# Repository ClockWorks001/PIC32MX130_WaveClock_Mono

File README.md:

# PIC32MX130F Speaking Clock Project.
---
This is a wave player  project with PIC32MX130 micro controller.
It can speak a "time" by using wave files which are stored in a SD card. 
And it also can play music wave files.

## Description

References.
  <http://microchip.wikidot.com/>

## Prerequisites

I created this project using the free versions of the following tools:
 * [Microchip MPLAB X][2] (v3.35)
 * [Microchip XC32 Compiler][3] (v1.3)
 * [EAGLE][6] (v4.0.1)

You will need to download and install these tools appropriately before you
can open this project and build it.
I use the [Microchip MPLAB PICkit3 In-Circuit Debugger][5] to program the chip and debug it.  

Also, I use the [EAGLE][6] to draw the electric circuit schematic.

## Licence

[MIT](https://github.com/tcnksm/tool/blob/master/LICENCE)

## Author

Hiroshi Murakami  
<https://github.com/ClockWorks001>  

[1]: http://ww1.microchip.com/downloads/en/DeviceDoc/60001168F.pdf "PIC32MXxxx"
[2]: http://www.microchip.com/pagehandler/en-us/family/mplabx/ "MPLAB X"
[3]: http://www.microchip.com/pagehandler/en_us/devtools/mplabxc/ "MPLAB XC Compilers"
[4]: http://www.microchip.com/harmony "MPLAB Harmony Configurator"
[5]: http://www.microchip.com/Developmenttools/ProductDetails.aspx?PartNO=PG164130 "MPLAB PICkit3 In-Circuit Debugger"
[6]: https://cadsoft.io/ "EAGLE"

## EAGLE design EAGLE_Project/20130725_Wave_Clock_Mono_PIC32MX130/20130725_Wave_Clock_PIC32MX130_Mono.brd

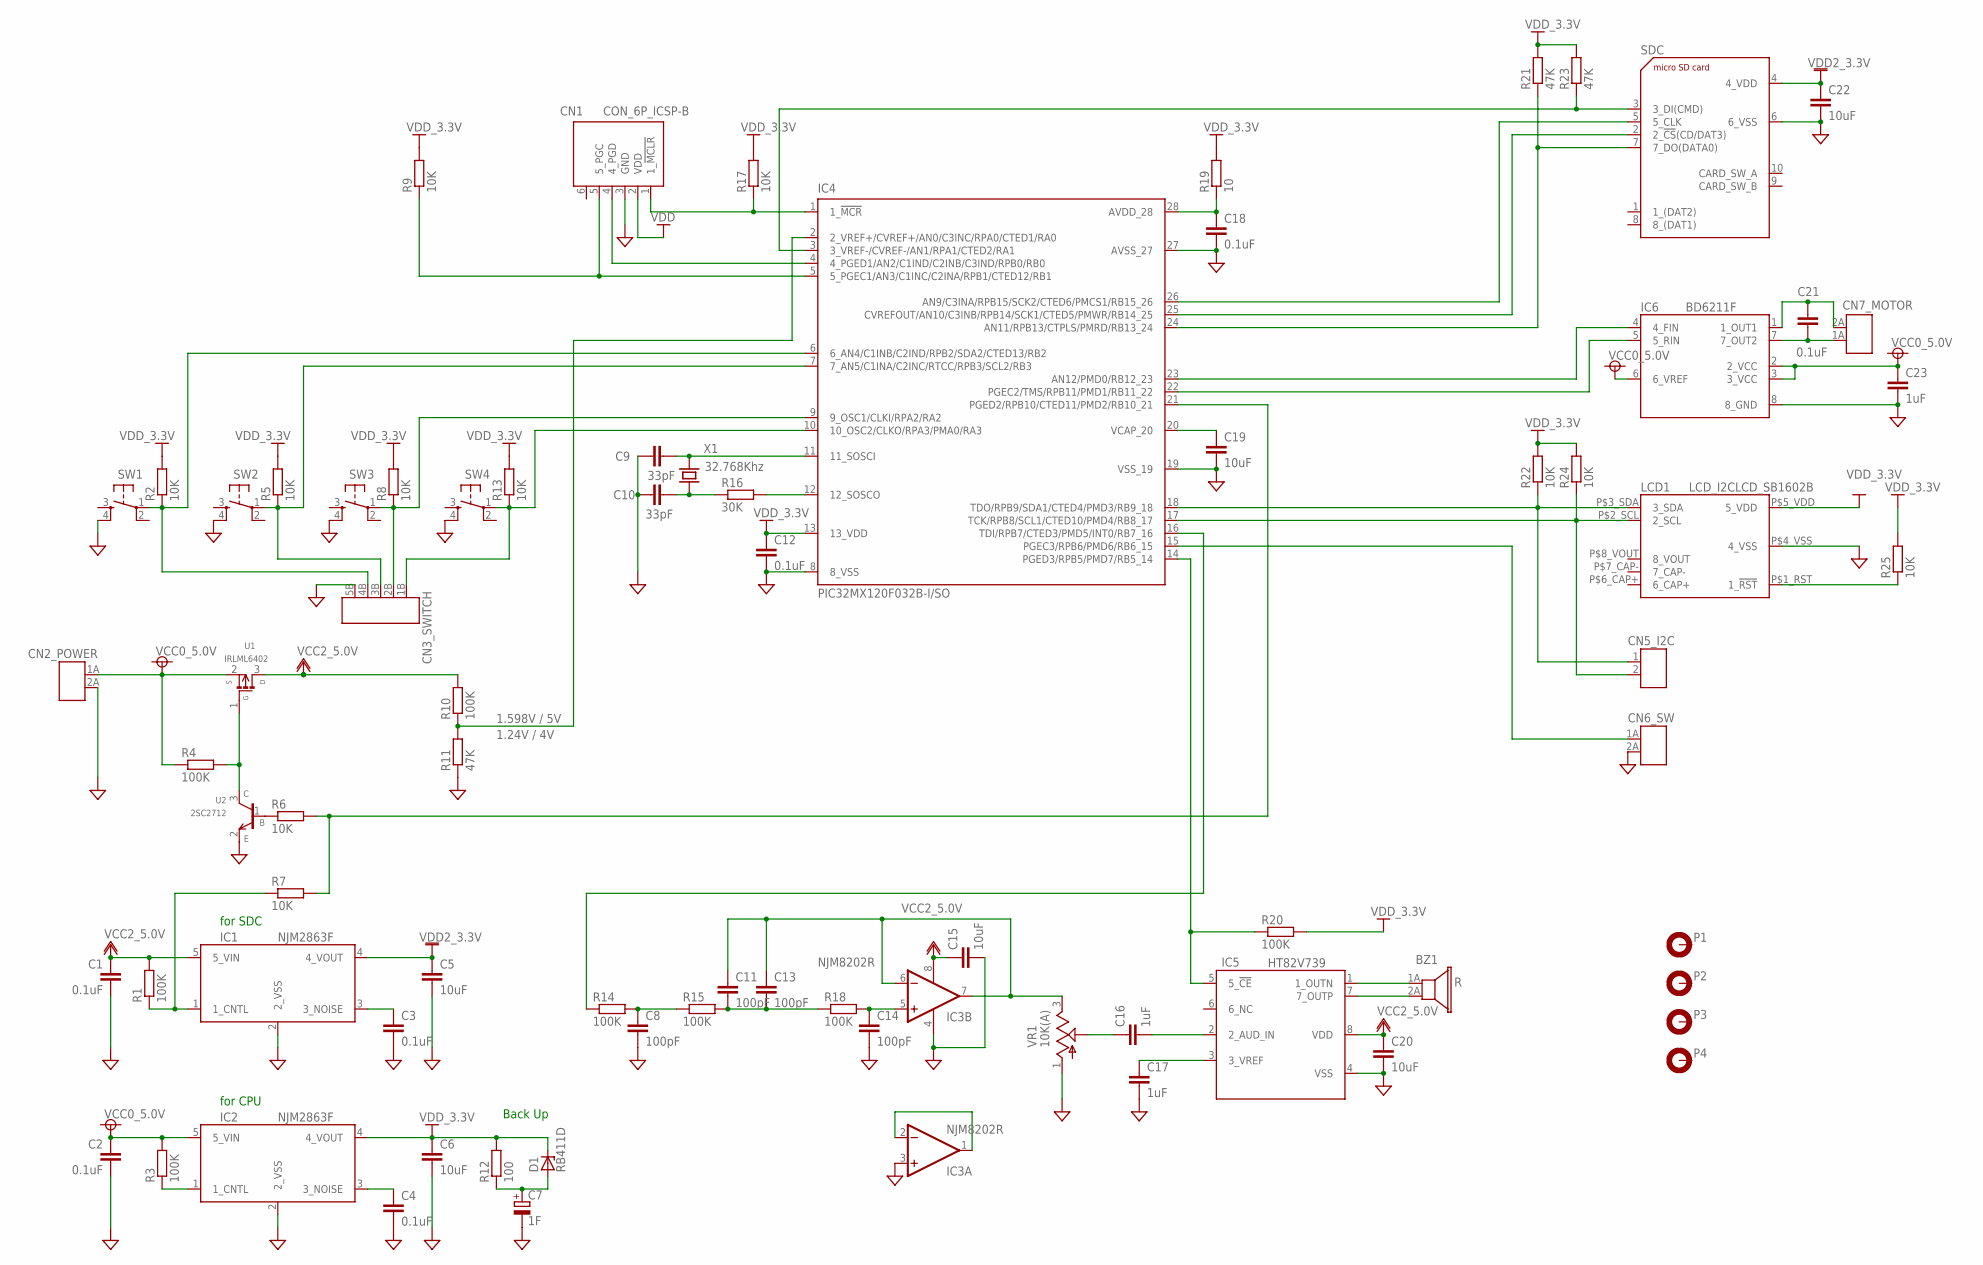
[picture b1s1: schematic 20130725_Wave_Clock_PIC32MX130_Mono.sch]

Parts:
BZ1: R; TERMINAL_AH-2P
C1, C2, C3, C4, C12, C18, C21: 0.1uF; 1608
C5, C6, C15, C19, C20, C22: 10uF; 3216
C7: 1F; E5-19V-B
C8, C11, C13, C14: 100pF; 1608
C9, C10: 33pF; 1608
C16, C17, C23: 1uF; 1608
CN1: CON_6P_ICSP-B; CON_DIP_6-B
CN2_POWER, CN6_SW, CN7_MOTOR: CON_2P-B; TERMINAL_AH-2P
CN3_SWITCH: CON_5PVR; TERMINAL_AV-5P
CN5_I2C: CON_2P-B; CON_DIP_2-B
D1: RB411D; SOT-23-3-2915-B
IC1, IC2: NJM2863F; SOT-23-5-2916-B
IC3: NJM8202R; MSOP08
IC4: PIC32MX120F032B-I/SO; SO28W
IC5: HT82V739; DIP08-B
IC6: BD6211F; SOP8
LCD1: LCD_I2CLCD_SB1602B; LCD_SB1602B
P1, P2, P3, P4: MOUNT-PAD3.3; PAD-3.3-B
R1, R3, R4, R10, R14, R15, R18, R20: 100K; 1608
R2, R5, R6, R7, R8, R9, R13, R17, R22, R24, R25: 10K; 1608
R11, R21, R23: 47K; 1608
R12: 100; 1608
R16: 30K; 1608
R19: 10; 1608
SDC: DM3AT-SF-PEJＤ; DM3AT-SF-DIP
SW1, SW2, SW3, SW4: SW_TACT1; SW_TACT-B
U1: IRLML6402; SC-59-2915
U2: 2SC2712; SOT-23-3-2915-B
VR1: 10K(A); VOL_MIDDLE
X1: 32.768Khz; VT-200

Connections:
GND: C1.2, C2.2, C3.2, C4.2, C5.2, C6.2, C7.-, C8.2, C9.2, C10.2, C12.2, C14.2, C15.2, C17.2, C18.2, C19.2, C20.2, C22.2, C23.2, CN1.3 (GND), CN2_POWER.2A (2), CN3_SWITCH.5B (5), CN6_SW.2A (2), IC1.2 (2_VSS), IC2.2 (2_VSS), IC3.3 (+IN), IC3.4 (V-), IC4.8 (8_VSS), IC4.19 (VSS_19), IC4.27 (AVSS_27), IC5.4 (VSS), IC6.8 (8_GND), LCD1.P$4_VSS (4_VSS), R11.1, SDC.6 (6_VSS), SW1.4 (S1), SW2.4 (S1), SW3.4 (S1), SW4.4 (S1), U2.2 (E), VR1.1 (A)
unnamed: CN1.1 (1_!MCLR), IC4.1 (1_!MCR), R17.1
unnamed: CN1.5 (5_PGC), IC4.5 (5_PGEC1/AN3/C1INC/C2INA/RPB1/CTED12/RB1), R9.1
unnamed: C18.1, IC4.28 (AVDD_28), R19.1
unnamed: C19.1, IC4.20 (VCAP_20)
unnamed: IC4.12 (12_SOSCO), R16.2
unnamed: C9.1, IC4.11 (11_SOSCI), X1.P$2 (2)
unnamed: CN1.4 (4_PGD), IC4.4 (4_PGED1/AN2/C1IND/C2INB/C3IND/RPB0/RB0)
unnamed: CN5_I2C.2, IC4.17 (TCK/RPB8/SCL1/CTED10/PMD4/RB8_17), LCD1.P$2_SCL (2_SCL), R24.1
unnamed: CN5_I2C.1, IC4.18 (TDO/RPB9/SDA1/CTED4/PMD3/RB9_18), LCD1.P$3_SDA (3_SDA), R22.1
unnamed: LCD1.P$1_RST (1_!RST), R25.1
unnamed: IC4.26 (AN9/C3INA/RPB15/SCK2/CTED6/PMCS1/RB15_26), SDC.5 (5_CLK)
unnamed: IC4.24 (AN11/RPB13/CTPLS/PMRD/RB13_24), R21.1, SDC.7 (7_DO(DATA0))
unnamed: IC4.25 (CVREFOUT/AN10/C3INB/RPB14/SCK1/CTED5/PM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), SDC.2 (2_!CS!(CD/DAT3))
unnamed: IC4.3 (3_VREF-/CVREF-/AN1/RPA1/CTED2/RA1), R23.1, SDC.3 (3_DI(CMD))
unnamed: CN3_SWITCH.2B (2), IC4.9 (9_OSC1/CLKI/RPA2/RA2), R8.1, SW3.1
unnamed: IC4.16 (TDI/RPB7/CTED3/PMD5/INT0/RB7_16), R14.1
unnamed: C14.1, IC3.5 (+IN), R18.2
unnamed: C8.1, R14.2, R15.1
unnamed: C11.2, C13.2, R15.2, R18.1
unnamed: IC3.1 (OUT), IC3.2 (-IN)
unnamed: CN6_SW.1A (1), IC4.15 (PGEC3/RPB6/PMD6/RB6_15)
unnamed: C17.1, IC5.3 (3_VREF)
unnamed: C16.2, IC5.2 (2_AUD_IN)
unnamed: BZ1.1A, IC5.1 (1_OUTN)
unnamed: BZ1.2A, IC5.7 (7_OUTP)
unnamed: C10.1, R16.1, X1.P$1 (1)
unnamed: R6.1, U2.1 (B)
unnamed: C16.1, VR1.2 (S)
unnamed: IC1.1 (1_CNTL), R1.1, R7.1
unnamed: C21.2, CN7_MOTOR.1A (1), IC6.7 (7_OUT2)
unnamed: C3.1, IC1.3 (3_NOISE)
unnamed: CN3_SWITCH.3B (3), IC4.7 (7_AN5/C1INA/C2INC/RTCC/RPB3/SCL2/RB3), R5.1, SW2.1
unnamed: C4.1, IC2.3 (3_NOISE)
unnamed: IC2.1 (1_CNTL), R3.1
unnamed: IC4.21 (PGED2/RPB10/CTED11/PMD2/RB10_21), R6.2, R7.2
unnamed: R4.2, U1.1 (G), U2.3 (C)
unnamed: CN3_SWITCH.4B (4), IC4.6 (6_AN4/C1INB/C2IND/RPB2/SDA2/CTED13/RB2), R2.1, SW1.1
unnamed: IC4.14 (PGED3/RPB5/PMD7/RB5_14), IC5.5 (5_!CE), R20.1
unnamed: CN3_SWITCH.1B (1), IC4.10 (10_OSC2/CLKO/RPA3/PMA0/RA3), R13.1, SW4.1
unnamed: C21.1, CN7_MOTOR.2A (2), IC6.1 (1_OUT1)
unnamed: C11.1, C13.1, IC3.6 (-IN), IC3.7 (OUT), VR1.3 (E)
unnamed: IC4.23 (AN12/PMD0/RB12_23), IC6.4 (4_FIN)
unnamed: IC4.22 (PGEC2/TMS/RPB11/PMD1/RB11_22), IC6.5 (5_RIN)
unnamed: IC4.2 (2_VREF+/CVREF+/AN0/C3INC/RPA0/CTED1/RA0), R10.1, R11.2
unnamed: C7.+, D1.1 (A), R12.1
VCC0: C2.1, C23.1, CN2_POWER.1A (1), IC2.5 (5_VIN), IC6.2 (2_VCC), IC6.3 (3_VCC), IC6.6 (6_VREF), R3.2, R4.1, U1.2 (S)
VCC2: C1.1, C15.1, C20.1, IC1.5 (5_VIN), IC3.8 (V+), IC5.8 (VDD), R1.2, R10.2, U1.3 (D)
VDD: C6.1, C12.1, CN1.2 (VDD), D1.3 (C), IC2.4 (4_VOUT), IC4.13 (13_VDD), LCD1.P$5_VDD (5_VDD), R2.2, R5.2, R8.2, R9.2, R12.2, R13.2, R17.2, R19.2, R20.2, R21.2, R22.2, R23.2, R24.2, R25.2
VDD2: C5.1, C22.1, IC1.4 (4_VOUT), SDC.4 (4_VDD)

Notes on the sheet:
for SDC
for CPU
Back Up
1.598V / 5V
1.24V / 4V

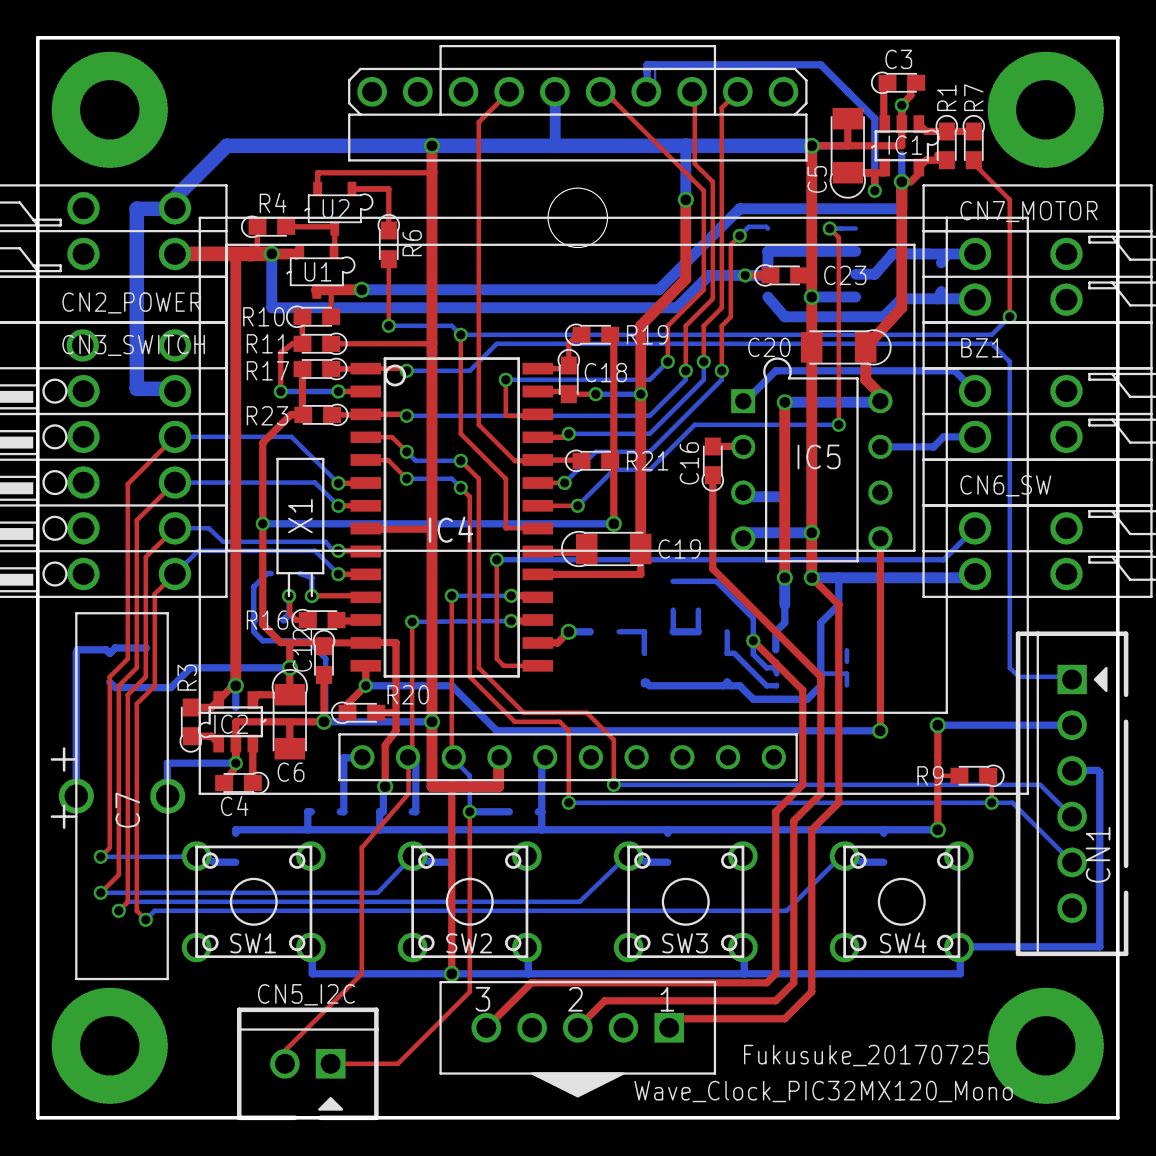
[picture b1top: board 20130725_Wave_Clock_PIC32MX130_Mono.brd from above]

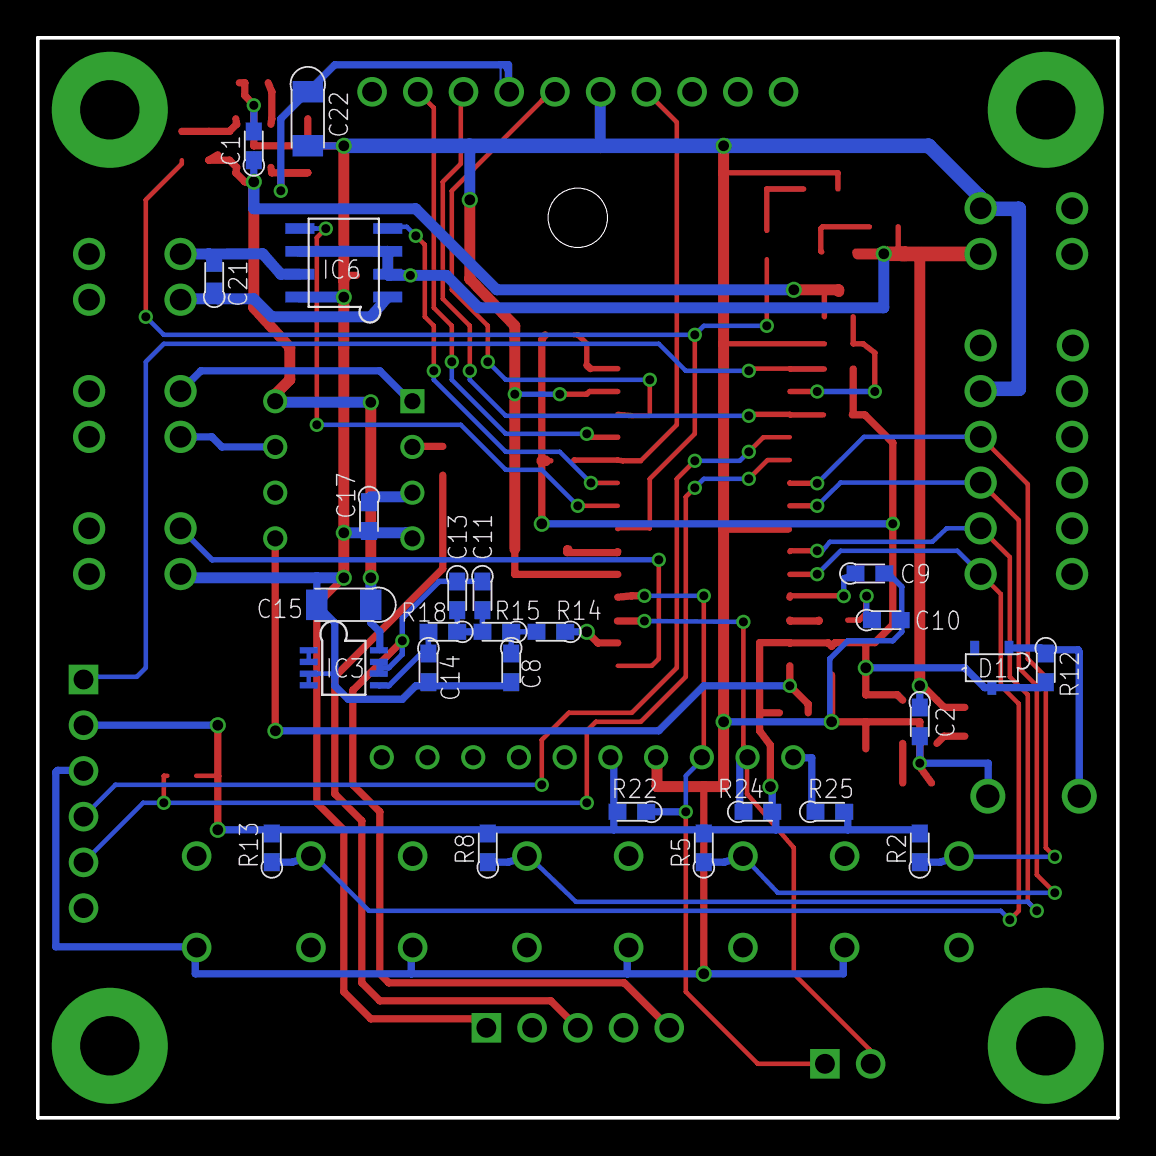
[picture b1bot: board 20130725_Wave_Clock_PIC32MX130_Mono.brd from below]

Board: 2 copper layers, 60.0 x 60.0 mm, 76 parts (26 on the bottom side), 50 nets.

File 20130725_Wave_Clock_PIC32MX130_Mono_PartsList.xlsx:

Parts List for
C:/app01/APIC/EAGLE/MyProject/20130725_Wave_Clock_Mono_PIC32MX120/20130725_Wave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
Parts Listing
Part | Value | Package | 購入店コウニュウテン
C7 | 1F | E5-19V-B | 秋月電子通商アキヅキ
C1 | 0.1uF | 1608 | 秋月電子通商アキヅキ
C2 | 0.1uF | 1608 | 秋月電子通商アキヅキ
C3 | 0.1uF | 1608 | 秋月電子通商アキヅキ
C4 | 0.1uF | 1608 | 秋月電子通商アキヅキ
C12 | 0.1uF | 1608 | 秋月電子通商アキヅキ
C17 | 0.1uF | 1608 | 秋月電子通商アキヅキ
C18 | 0.1uF | 1608 | 秋月電子通商アキヅキ
C21 | 0.1uF | 1608 | 秋月電子通商アキヅキ
C8 | 100pF | 1608 | 秋月電子通商アキヅキ
C11 | 100pF | 1608 | 秋月電子通商アキヅキ
C13 | 100pF | 1608 | 秋月電子通商アキヅキ
C14 | 100pF | 1608 | 秋月電子通商アキヅキ
C5 | 10uF | 3216 | 秋月電子通商アキヅキ
C6 | 10uF | 3216 | 秋月電子通商アキヅキ
C15 | 10uF | 3216 | 秋月電子通商アキヅキ
C19 | 10uF | 3216 | 秋月電子通商アキヅキ
C20 | 10uF | 3216 | 秋月電子通商アキヅキ
C22 | 10uF | 3216 | 秋月電子通商アキヅキ
C16 | 1uF | 1608 | 秋月電子通商アキヅキ
C23 | 1uF | 1608 | 秋月電子通商アキヅキ
C9 | 33pF | 1608 | 秋月電子通商アキヅキ
C10 | 33pF | 1608 | 秋月電子通商アキヅキ
BZ1 | R | TERMINAL_AH-2P | 秋月電子通商アキヅキ
CN2_POWER | CON_2P-B | TERMINAL_AH-2P | 秋月電子通商アキヅキ
CN6_SW | CON_2P-B | TERMINAL_AH-2P | 秋月電子通商アキヅキ
CN7_MOTOR | CON_2P-B | TERMINAL_AH-2P | 秋月電子通商アキヅキ
CN3_SWITCH | CON_5PVR | TERMINAL_AV-5P | 秋月電子通商アキヅキ
CN5_I2C | CON_2P-B | CON_DIP_2-B | 秋月電子通商アキヅキ
CN1 | CON_6P_ICSP-B | CON_DIP_6-B | 秋月電子通商アキヅキ
D1 | RB411D | SOT-23-3-2915-B | 秋月電子通商アキヅキ
IC1 | NJM2863F | SOT-23-5-2916-B | 秋月電子通商アキヅキ
IC2 | NJM2863F | SOT-23-5-2916-B | 秋月電子通商アキヅキ
IC3 | NJM8202R | MSOP08 | 秋月電子通商アキヅキ
IC4 | PIC32MX120F032B-I/SO | SO28W | digkey
IC5 | HT82V739 | DIP08-B | 秋月電子通商アキヅキ
IC6 | BD6211F | SOP8 | 秋月電子通商アキヅキ
LCD1 | LCD_I2CLCD_SB1602B | LCD_SB1602B | ストロベリーリナックス
R19 | 10 | 1608 | 秋月電子通商アキヅキ
R12 | 100 | 1608 | 秋月電子通商アキヅキ
R1 | 100K | 1608 | 秋月電子通商アキヅキ
R3 | 100K | 1608 | 秋月電子通商アキヅキ
R4 | 100K | 1608 | 秋月電子通商アキヅキ
R10 | 100K | 1608 | 秋月電子通商アキヅキ
R14 | 100K | 1608 | 秋月電子通商アキヅキ
R15 | 100K | 1608 | 秋月電子通商アキヅキ
R18 | 100K | 1608 | 秋月電子通商アキヅキ
R20 | 100K | 1608 | 秋月電子通商アキヅキ
R2 | 10K | 1608 | 秋月電子通商アキヅキ
R5 | 10K | 1608 | 秋月電子通商アキヅキ
R6 | 10K | 1608 | 秋月電子通商アキヅキ
R7 | 10K | 1608 | 秋月電子通商アキヅキ
R8 | 10K | 1608 | 秋月電子通商アキヅキ
R9 | 10K | 1608 | 秋月電子通商アキヅキ
R13 | 10K | 1608 | 秋月電子通商アキヅキ
R17 | 10K | 1608 | 秋月電子通商アキヅキ
R22 | 10K | 1608 | 秋月電子通商アキヅキ
R24 | 10K | 1608 | 秋月電子通商アキヅキ
R25 | 10K | 1608 | 秋月電子通商アキヅキ
R16 | 30K | 1608 | 秋月電子通商アキヅキ
R11 | 47K | 1608 | 秋月電子通商アキヅキ
R21 | 47K | 1608 | 秋月電子通商アキヅキ
R23 | 47K | 1608 | 秋月電子通商アキヅキ
SDC | DM3AT-SF-PEJc | DM3AT-SF-DIP | 秋月電子通商アキヅキ
SW1 | SW_TACT1 | SW_TACT-B | 秋月電子通商アキヅキ
SW2 | SW_TACT1 | SW_TACT-B | 秋月電子通商アキヅキ
SW3 | SW_TACT1 | SW_TACT-B | 秋月電子通商アキヅキ
SW4 | SW_TACT1 | SW_TACT-B | 秋月電子通商アキヅキ
U1 | IRLML6402 | SC-59-2915 | 秋月電子通商アキヅキ
U2 | 2SC2712 | SOT-23-3-2915-B | 秋月電子通商アキヅキ
VR1 | 50K 10K(A) | VOL_MIDDLE | 秋月電子通商アキヅキ
X1 | 32.768Khz | VT-200 | 秋月電子通商アキヅキ
Generated by PART2HTM v0.4 by Sean D. Alcorn
© 1997 Avion International Co. Ltd.
Bangkok • Sydney • Taipei
 | 電池ボックスデンチ | 1
 | スピーカ | 1

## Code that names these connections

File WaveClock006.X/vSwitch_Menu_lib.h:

/*************************************************
*  Switch_Menu処理ヘッダファイル
*    vPushSwitch_init()  ----- 初期化
*    vSW2_Check() ----- SW2_ チェック＆repeat処理
*    vSW2_UserHandling() ----- SW2_が押された時のユーザ処理を記述する
*    char cSW2_ON() ----- SW2_の状態を返信する。フラグをクリアする。
*    vSW1_Check() ----- SW1_ チェック＆repeat処理
*    vSW1_UserHandling() ----- SW2_が押された時のユーザ処理を記述する
*************************************************/

//pushbuttons define
#define SW1		PORTBbits.RB2	//bring forward the Switch menu status
#define SW2		PORTBbits.RB3	//for Number Addition
#define SW3		PORTAbits.RA2	//for Number Subtraction
#define SW4		PORTAbits.RA3	//for cancellation
#define SWITCH_ON		1
#define SWITCH_OFF		0
#define FILE_NAME_BUFFER_SIZE 30			//File Name buffer size


/*****************************
** 定数変数定義
*****************************/
	enum eModeS1 {
		eModeS1_clock,			// idle

		// Switch Main Menu control
		eModeS1_ModeSelect_pre,
		eModeS1_ModeSelect,
		eModeS1_ModeSelect_jmp,
		eModeS1_ModeSelect_jmp_wave_play,
		eModeS1_ModeSelect_jmp_Time_set,
		eModeS1_ModeSelect_jmp_Date_set,
		eModeS1_ModeSelect_jmp_Chime_Enable,
		eModeS1_ModeSelect_jmp_Chime_Disable,

		// Time Date set Menu control
		eModeS1_Time_set_pre,
		eModeS1_1H_set,
		eModeS1_1M_set,
		eModeS1_Time_set_desision_pre,
		eModeS1_Time_set_desision,
		eModeS1_Time_set_desision_jmp,
		eModeS1_Time_set,
		eModeS1_Time_set_cancel,

		eModeS1_Date_set_pre,
		eModeS1_1Year_set,
		eModeS1_1Month_set,
		eModeS1_1Day_set,
		eModeS1_Date_set_desision_pre,
		eModeS1_Date_set_desision,
		eModeS1_Date_set_desision_jmp,
		eModeS1_Date_set,
		eModeS1_Date_set_cancel,

		// Wave Play Menu control
		eModeS1_search_music_pre,
		eModeS1_search_music_dir,
		eModeS1_play_music,
		eModeS1_repeat_music,

		// other control
		//eModeS1_sleep,

		eModeS1_end
	};

#if defined SWITCH_MENU_LIB
	char cSW2_flag = 0;		// global変数はstaticは、要らない
	char cSW3_flag = 0;		// global変数はstaticは、要らない
	char cSW4_flag = 0;		// global変数はstaticは、要らない
	int iSelectNo01;		// 制御selectする場合の番号保持用

	BYTE bFileName_buff[FILE_NAME_BUFFER_SIZE + 1];	//File Name buffer
	unsigned char ucMin02, ucHour02;	//時刻設定用

	enum eModeS1 eModeSwitchStatus1;

#else
	//extern char ucTestCount = 0;
	extern enum eModeS1 eModeSwitchStatus1;
#endif


/*****************************
*  プロトタイプ定義ファイル
*****************************/
void vPushSwitch_init(void);
void vSW2_Check(void);
void vSW2_UserHandling(void);
char cSW2_ON(void);
void vSW1_Check(void);
void vSW1_UserHandling(void);
void vSW3_Check(void);
void vSW3_UserHandling(void);
char cSW3_ON(void);
void vSW4_Check(void);
void vSW4_UserHandling(void);
char cSW4_ON(void);
void vModeSwitchControl00(void);
void vModeSwitchControl01(void);
void vModeSwitchControl02(void);

int iAddNumber(int iNowNumber, int iAddNumber, int iMinNumber, int iMaxNumber);
int iSubNumber(int iNowNumber, int iSubNumber, int iMinNumber, int iMaxNumber);
void vPowerSave(void);

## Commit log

2016-11-13 add briefing document
2016-11-23 add assemble explanation and photos
2016-11-24 added case assembly information.
2016-11-24 added JWCAD data
2016-11-24 added case assembly note
2016-11-24 updated case assembly note
2016-12-01 updated the case assenble documents
2016-12-05 amended xc32 compiler version to v1.3
2016-12-07 added WDT peripheral
2017-01-11 add CheckProject.X
2017-01-12 amended CheckProject.X. added volatile
